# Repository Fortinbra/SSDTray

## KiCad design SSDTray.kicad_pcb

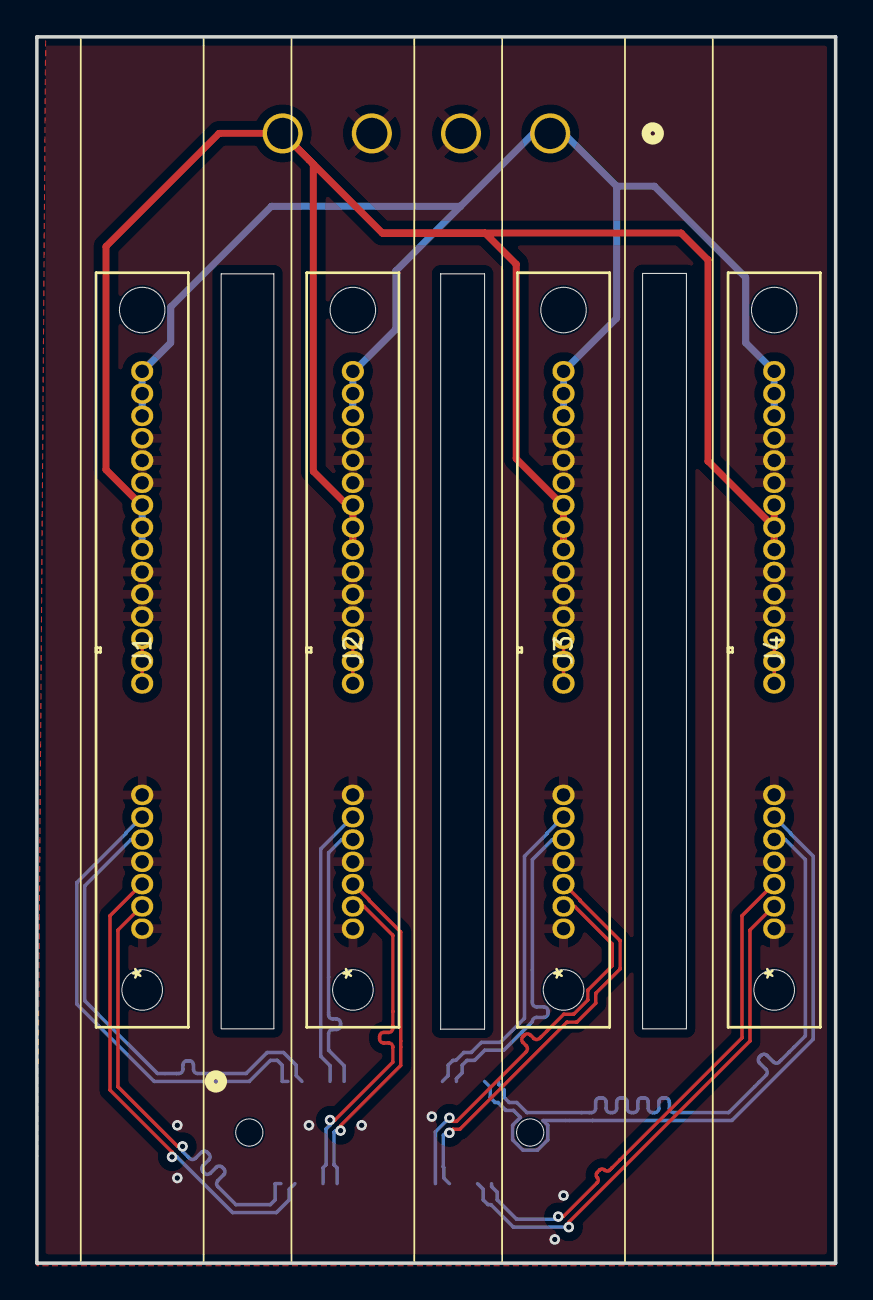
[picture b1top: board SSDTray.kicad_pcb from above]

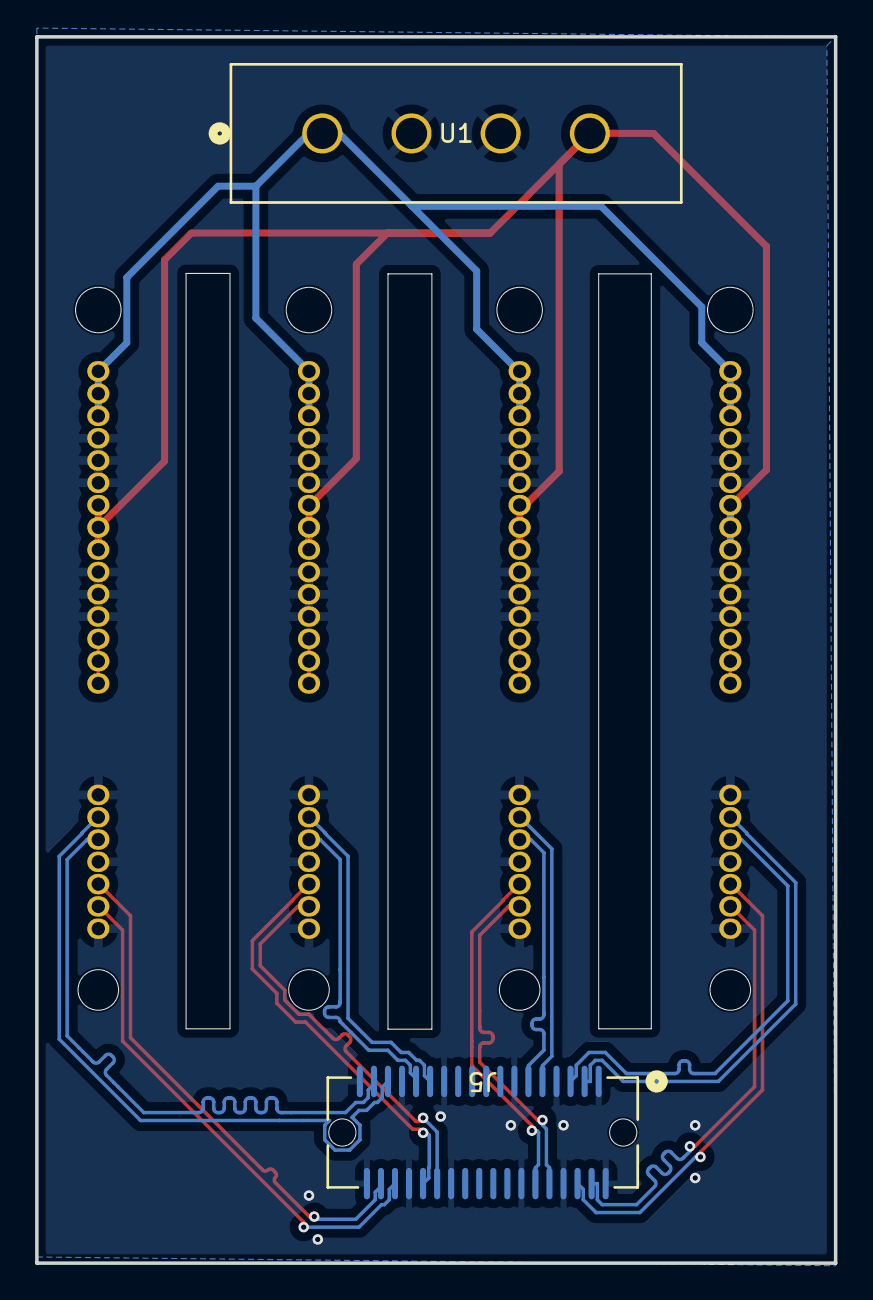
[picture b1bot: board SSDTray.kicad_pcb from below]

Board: 4 copper layers, 45.5 x 69.8 mm, 6 parts (2 on the bottom side), 19 nets.

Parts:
J1: SSD1; CONN_877791001_MOL
J2: SSD2; CONN_877791001_MOL
J3: SSD3; CONN_877791001_MOL
J4: SSD4; CONN_877791001_MOL
J5: 1888020-4; CONN36_1888020-4_TEC
U1: 350211-1; 350211-1_TYC

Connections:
+5V: J1.P7, J1.P8, J1.P9, J2.P7, J2.P8, J2.P9, J3.P7, J3.P8, J3.P9, J4.P7, J4.P8, J4.P9, U1.4
+12V: J1.P13, J1.P14, J1.P15, J2.P13, J2.P14, J2.P15, J3.P13, J3.P14, J3.P15, J4.P13, J4.P14, J4.P15, U1.1
/SSD1_RX+: J1.S6, J5.A2
/SSD1_RX-: J1.S5, J5.A3
/SSD1_TX+: J1.S2, J5.B2
/SSD1_TX-: J1.S3, J5.B3
/SSD2_RX+: J2.S6, J5.A5
/SSD2_RX-: J2.S5, J5.A6
/SSD2_TX+: J2.S2, J5.B5
/SSD2_TX-: J2.S3, J5.B6
/SSD3_RX+: J3.S6, J5.A13
/SSD3_RX-: J3.S5, J5.A14
/SSD3_TX+: J3.S2, J5.B13
/SSD3_TX-: J3.S3, J5.B14
/SSD4_RX+: J4.S6, J5.A16
/SSD4_RX-: J4.S5, J5.A17
/SSD4_TX+: J4.S2, J5.B16
/SSD4_TX-: J4.S3, J5.B17
GND: J1.P4, J1.P5, J1.P6, J1.P10, J1.P11, J1.P12, J1.S1, J1.S4, J1.S7, J2.P4, J2.P5, J2.P6, J2.P10, J2.P11, J2.P12, J2.S1, J2.S4, J2.S7, J3.P4, J3.P5, J3.P6, J3.P10, J3.P11, J3.P12, J3.S1, J3.S4, J3.S7, J4.P4, J4.P5, J4.P6, J4.P10, J4.P11, J4.P12, J4.S1, J4.S4, J4.S7, J5.A1, J5.A4, J5.A7, J5.A12, J5.A15, J5.A18, J5.B1, J5.B4, J5.B7, J5.B12, J5.B15, J5.B18, U1.2, U1.3

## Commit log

2025-01-23 Initial
2025-01-23 Remove autosave lock file and update active layer preset to 'All Layers'
2025-01-23 Add .gitignore for KiCad project and remove obsolete SSDTray.kicad_prl file
2025-01-25 Add Molex Connector footprint and symbol to libraries
2025-01-25 No code changes made.
2025-01-29 Add Mini SAS footprint and symbol to libraries; update design rules and dimensions in SSDTray.kicad_pro
2025-02-14 Limiting to 4 drives for testing
2025-03-24 confused now
